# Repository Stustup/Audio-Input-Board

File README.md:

# Audio Input Board

A simple input board to interface multiple connectors with DIY projects. I use it mainly as connector boards for prototyping tube amps, which are wired point to point. Adding flimsy cables with connectors soldered to them was and would be tedious. 
Also this makes it possible to securely attach oscilloscope probes on the test holes.

## Connectors on the board are:
1. 3.5mm Stereo Jack
2. 2 Stereo Chinch/RCA connectors (for input/output)
3. 4.4mm Differential Pentaconn connector, because i like it and want to push it.
3. 4 Mono Differential XLR connectors (for input/output). One could use each of these as a single stereo Jack 

To interface these connectors to your DIY project you need a few JST_EH P2.50mm connectors and cables, which are the (it looks like to me) standard for cheap knock off DIY connectors in sets on eBay. 

You could also just solder wires to the holes corresponding to the input jack.

The XLR connectors wre wired somewhat weirdly, like you can see in the next picture:

As you can see, the top pins are the hot pins and the bottom pins are the cold pins. Use this as you like. The pin 1 of the XLR (used for ground or Earth) is connected only to the GND plane on the XLR side. To connect this to the GND of the single ended Jacks (RCA and 3.5mm) and the pentaconn one you have to solder the little "Earth_Con" jumper. 

The switched contacts of the 3.5mm jack are broken out, too.

## Notes

The 3D models of the connectors are not in this repository, you can grab these on GrabCAD.

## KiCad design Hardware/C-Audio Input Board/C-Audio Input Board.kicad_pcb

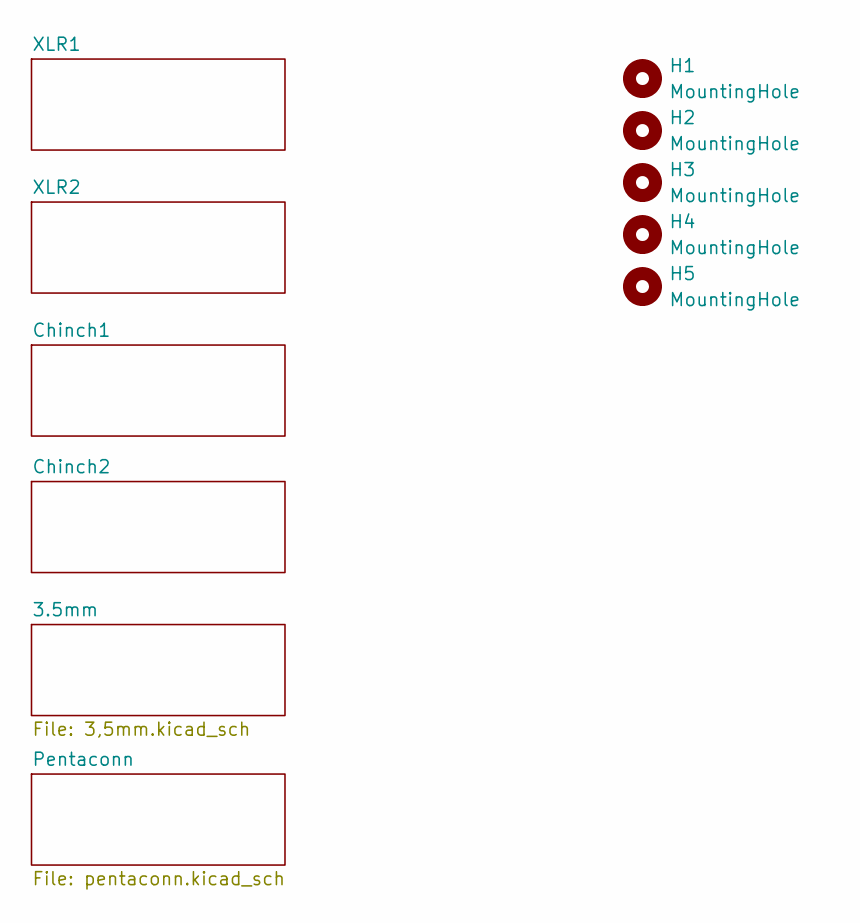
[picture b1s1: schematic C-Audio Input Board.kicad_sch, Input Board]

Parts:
H1, H2, H3, H4, H5: MountingHole; MountingHole_3.5mm

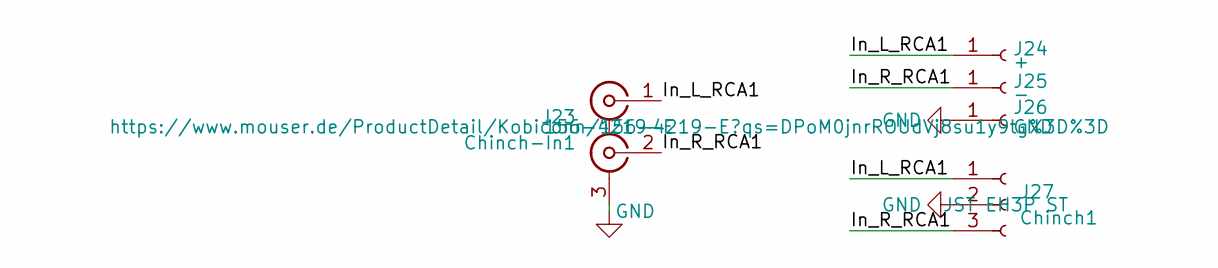
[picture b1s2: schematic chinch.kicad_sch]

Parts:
J23: Chinch-In1; CBP 2; Mouser Nr. 156-4219-E
J24: +; Pin_D1.3mm_L11.0mm
J25: -; Pin_D1.3mm_L11.0mm
J26: GND; Pin_D1.3mm_L11.0mm
J27: Chinch1; JST_EH_B3B-EH-A_1x03_P2.50mm_Vertical

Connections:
/Chinch1/In_L_RCA1: J23.1 (IN1), J24.1, J27.1
/Chinch1/In_R_RCA1: J23.2 (IN2), J25.1, J27.3
GND: J23.3 (EXT), J26.1, J27.2; also elsewhere on the board

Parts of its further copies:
J28: Chinch-In1; CBP 2; Mouser Nr. 156-4219-E
J29: +; Pin_D1.3mm_L11.0mm
J30: -; Pin_D1.3mm_L11.0mm
J31: GND; Pin_D1.3mm_L11.0mm
J32: Chinch1; JST_EH_B3B-EH-A_1x03_P2.50mm_Vertical

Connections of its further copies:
/Chinch2/In_L_RCA1: J28.1 (IN1), J29.1, J32.1
/Chinch2/In_R_RCA1: J28.2 (IN2), J30.1, J32.3
GND: J28.3 (EXT), J31.1, J32.2; also elsewhere on the board

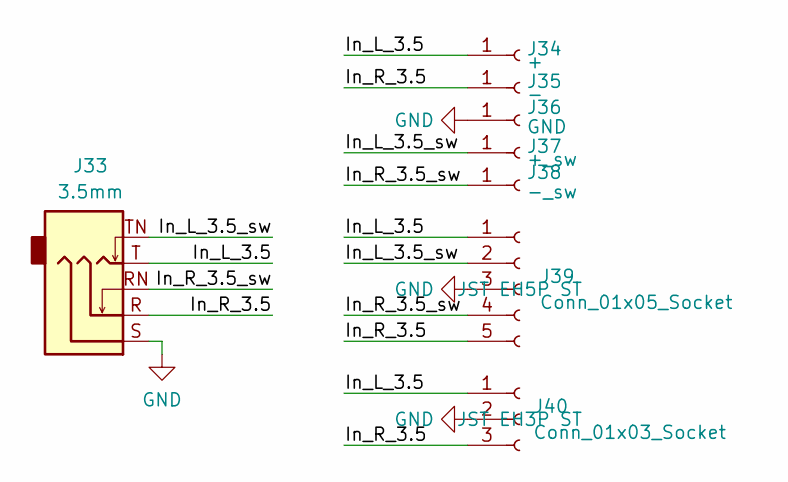
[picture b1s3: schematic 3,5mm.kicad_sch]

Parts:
J33: 3.5mm; Jack_3.5mm_Ledino_KB3SPRS_Horizontal
J34: +; Pin_D1.3mm_L11.0mm
J35: -; Pin_D1.3mm_L11.0mm
J36: GND; Pin_D1.3mm_L11.0mm
J37: +_sw; Pin_D1.3mm_L11.0mm
J38: -_sw; Pin_D1.3mm_L11.0mm
J39: Conn_01x05_Socket; JST_EH_B5B-EH-A_1x05_P2.50mm_Vertical
J40: Conn_01x03_Socket; JST_EH_B3B-EH-A_1x03_P2.50mm_Vertical

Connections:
/3.5mm/In_L_3.5: J33.T, J34.1, J39.1, J40.1
/3.5mm/In_L_3.5_sw: J33.TN, J37.1, J39.2
/3.5mm/In_R_3.5: J33.R, J35.1, J39.5, J40.3
/3.5mm/In_R_3.5_sw: J33.RN, J38.1, J39.4
GND: J33.S, J36.1, J39.3, J40.2; also elsewhere on the board

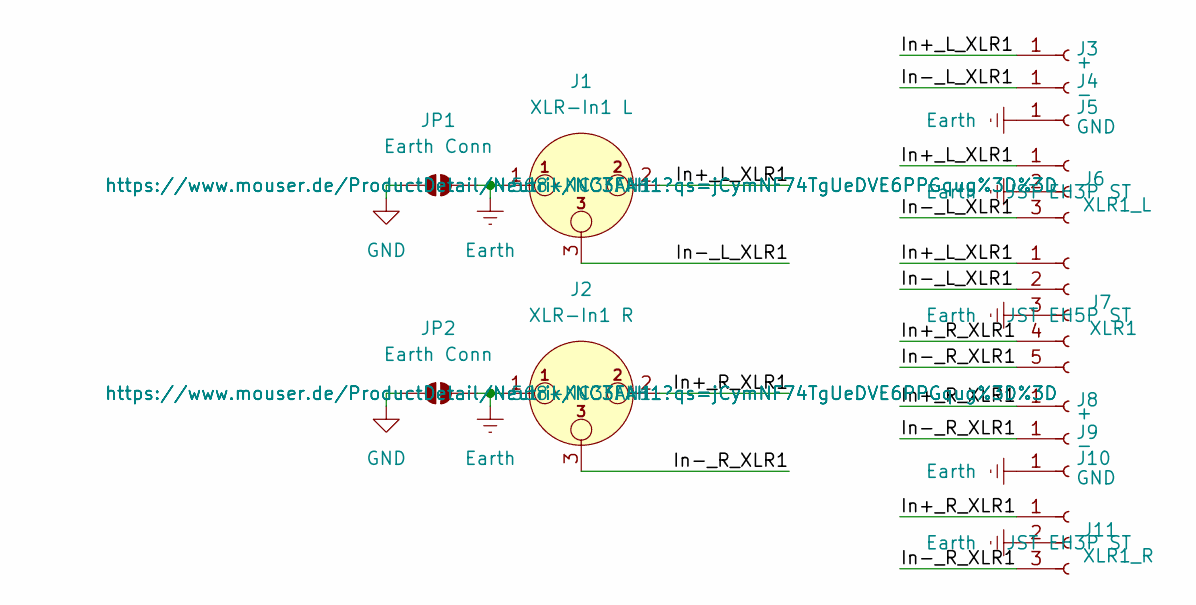
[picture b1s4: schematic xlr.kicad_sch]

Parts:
J1: XLR-In1 L; Jack_XLR_Neutrik_NC3FAH1_Horizontal; Mouser Nr. 568-NC3FAH1
J2: XLR-In1 R; Jack_XLR_Neutrik_NC3FAH1_Horizontal; Mouser Nr. 568-NC3FAH1
J3, J8: +; Pin_D1.3mm_L11.0mm
J4, J9: -; Pin_D1.3mm_L11.0mm
J5, J10: GND; Pin_D1.3mm_L11.0mm
J6: XLR1_L; JST_EH_B3B-EH-A_1x03_P2.50mm_Vertical
J7: XLR1; JST_EH_B5B-EH-A_1x05_P2.50mm_Vertical
J11: XLR1_R; JST_EH_B3B-EH-A_1x03_P2.50mm_Vertical
JP1, JP2: Earth Conn; SolderJumper-2_P1.3mm_Open_TrianglePad1.0x1.5mm

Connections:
/XLR1/In+_L_XLR1: J1.2, J3.1, J6.1, J7.1
/XLR1/In+_R_XLR1: J2.2, J7.4, J8.1, J11.1
/XLR1/In-_L_XLR1: J1.3, J4.1, J6.3, J7.2
/XLR1/In-_R_XLR1: J2.3, J7.5, J9.1, J11.3
Earth: J1.1, J2.1, J5.1, J6.2, J7.3, J10.1, J11.2, JP1.2 (B), JP2.2 (B); also elsewhere on the board
GND: JP1.1 (A), JP2.1 (A); also elsewhere on the board

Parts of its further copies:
J12: XLR-In1 L; Jack_XLR_Neutrik_NC3FAH1_Horizontal; Mouser Nr. 568-NC3FAH1
J13: XLR-In1 R; Jack_XLR_Neutrik_NC3FAH1_Horizontal; Mouser Nr. 568-NC3FAH1
J14, J19: +; Pin_D1.3mm_L11.0mm
J15, J20: -; Pin_D1.3mm_L11.0mm
J16, J21: GND; Pin_D1.3mm_L11.0mm
J17: XLR1_L; JST_EH_B3B-EH-A_1x03_P2.50mm_Vertical
J18: XLR1; JST_EH_B5B-EH-A_1x05_P2.50mm_Vertical
J22: XLR1_R; JST_EH_B3B-EH-A_1x03_P2.50mm_Vertical

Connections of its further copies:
/XLR2/In+_L_XLR1: J12.2, J14.1, J17.1, J18.1
/XLR2/In+_R_XLR1: J13.2, J18.4, J19.1, J22.1
/XLR2/In-_L_XLR1: J12.3, J15.1, J17.3, J18.2
/XLR2/In-_R_XLR1: J13.3, J18.5, J20.1, J22.3
Earth: J12.1, J13.1, J16.1, J17.2, J18.3, J21.1, J22.2; also elsewhere on the board

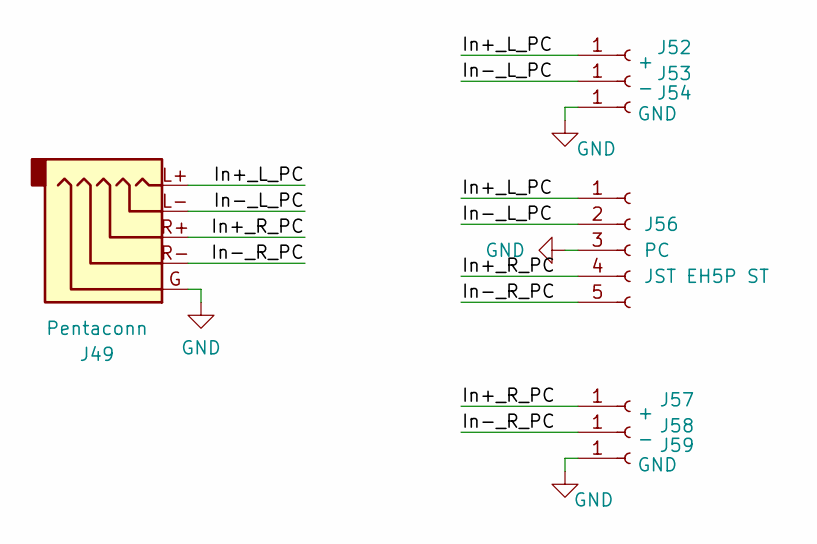
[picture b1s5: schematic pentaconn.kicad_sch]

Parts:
J49: Pentaconn
J52, J57: +; Pin_D1.3mm_L11.0mm
J53, J58: -; Pin_D1.3mm_L11.0mm
J54, J59: GND; Pin_D1.3mm_L11.0mm
J56: PC; JST_EH_B5B-EH-A_1x05_P2.50mm_Vertical

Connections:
/Pentaconn/In+_L_PC: J49.L+, J52.1, J56.1
/Pentaconn/In+_R_PC: J49.R+, J56.4, J57.1
/Pentaconn/In-_L_PC: J49.L-, J53.1, J56.2
/Pentaconn/In-_R_PC: J49.R-, J56.5, J58.1
GND: J49.G, J54.1, J56.3, J59.1; also elsewhere on the board

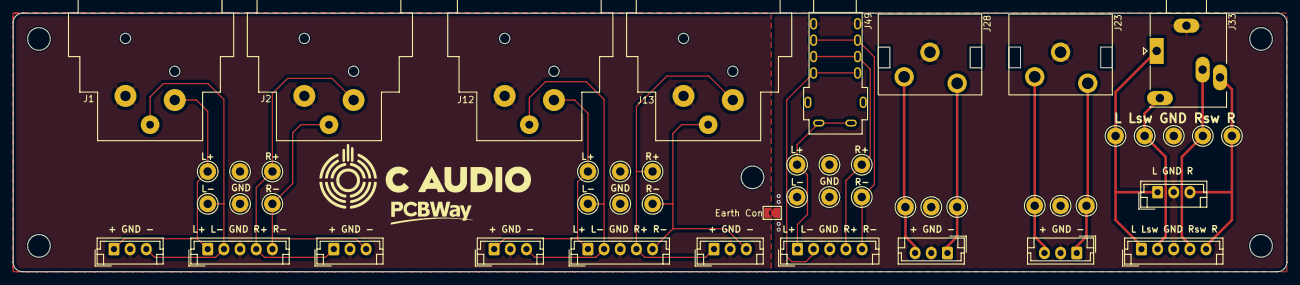
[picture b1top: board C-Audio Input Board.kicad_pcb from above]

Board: 2 copper layers, 196.9 x 39.9 mm, 54 parts (0 on the bottom side), 22 nets.

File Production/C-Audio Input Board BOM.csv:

Reference,Value,Datasheet,Footprint,Qty,DNP,Mouser Link,Reichelt Nr.,Reichelt Link,Mouser Nr.
"J1,J12",XLR-In1 L,https://www.neutrik.com/en/product/nc3fah1,Connector_Audio:Jack_XLR_Neutrik_NC3FAH1_Horizontal,2,,https://www.mouser.de/ProductDetail/Neutrik/NC3FAH1?qs=jCymN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,,, 568-NC3FAH1 
"J2,J13",XLR-In1 R,https://www.neutrik.com/en/product/nc3fah1,Connector_Audio:Jack_XLR_Neutrik_NC3FAH1_Horizontal,2,,https://www.mouser.de/ProductDetail/Neutrik/NC3FAH1?qs=jCymN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,,, 568-NC3FAH1 
"J3,J8,J14,J19,J24,J29,J34",+,~,Connector_Pin:Pin_D1.3mm_L11.0mm,7,,,,,
"J4,J9,J15,J20,J25,J30,J35",-,~,Connector_Pin:Pin_D1.3mm_L11.0mm,7,,,,,
"J5,J10,J16,J21,J26,J31,J36",GND,~,Connector_Pin:Pin_D1.3mm_L11.0mm,7,,,,,
"J6,J17",XLR1_L,~,Connector_JST:JST_EH_B3B-EH-A_1x03_P2.50mm_Vertical,2,,, JST EH3P ST,,
"J7,J18",XLR1,~,Connector_JST:JST_EH_B5B-EH-A_1x05_P2.50mm_Vertical,2,,,JST EH5P ST,,
"J11,J22",XLR1_R,~,Connector_JST:JST_EH_B3B-EH-A_1x03_P2.50mm_Vertical,2,,, JST EH3P ST,,
"J23,J28",Chinch-In1,https://www.mouser.de/datasheet/2/209/KC_2032021_1-2580140.pdf,_lib:CBP 2,2,,https://www.mouser.de/ProductDetail/Kobiconn/156-4219-E?qs=D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,,, 156-4219-E 
"J27,J32",Chinch1,~,Connector_JST:JST_EH_B3B-EH-A_1x03_P2.50mm_Vertical,2,,, JST EH3P ST,,
J33,3.5mm,~,Connector_Audio:Jack_3.5mm_Ledino_KB3SPRS_Horizontal,1,,,EBS 35,https://www.reichelt.de/de/de/shop/produkt/klinkeneinbaubuch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,
J37,+_sw,~,Connector_Pin:Pin_D1.3mm_L11.0mm,1,,,,,
J38,-_sw,~,Connector_Pin:Pin_D1.3mm_L11.0mm,1,,,,,
J39,Conn_01x05_Socket,~,Connector_JST:JST_EH_B5B-EH-A_1x05_P2.50mm_Vertical,1,,,JST EH5P ST,,
J40,Conn_01x03_Socket,~,Connector_JST:JST_EH_B3B-EH-A_1x03_P2.50mm_Vertical,1,,, JST EH3P ST,,

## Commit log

2025-03-06 wrote README file
2025-03-06 readme improvement
2025-03-06 Added legal notice for 3d models
2025-03-10 added mouser and reichelt numbers to BOM
2025-03-10 test
2025-03-10 added BOM
2025-03-10 bom directory
2025-03-19 Create LICENSE
2026-03-11 added pentaconn and silkscreen marking. Also added PCBWay logo for sponsorship
2026-03-11 added BOM and new gerbers
2026-03-11 updated README and 3D Models
2026-03-11 added new 3D model#
2026-03-11 cleanup
2026-03-12 finalized Silkscreen and production data
